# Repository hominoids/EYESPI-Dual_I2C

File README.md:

# EYESPI-Dual_I2C

## Introduction
EYESPI-Dual_I2C is an EYESPI display port and dual I2C 5 port hubs that can be deployed with passive or active termination on most SBC using their 40 pin GPIO. 

License: GPLv3.

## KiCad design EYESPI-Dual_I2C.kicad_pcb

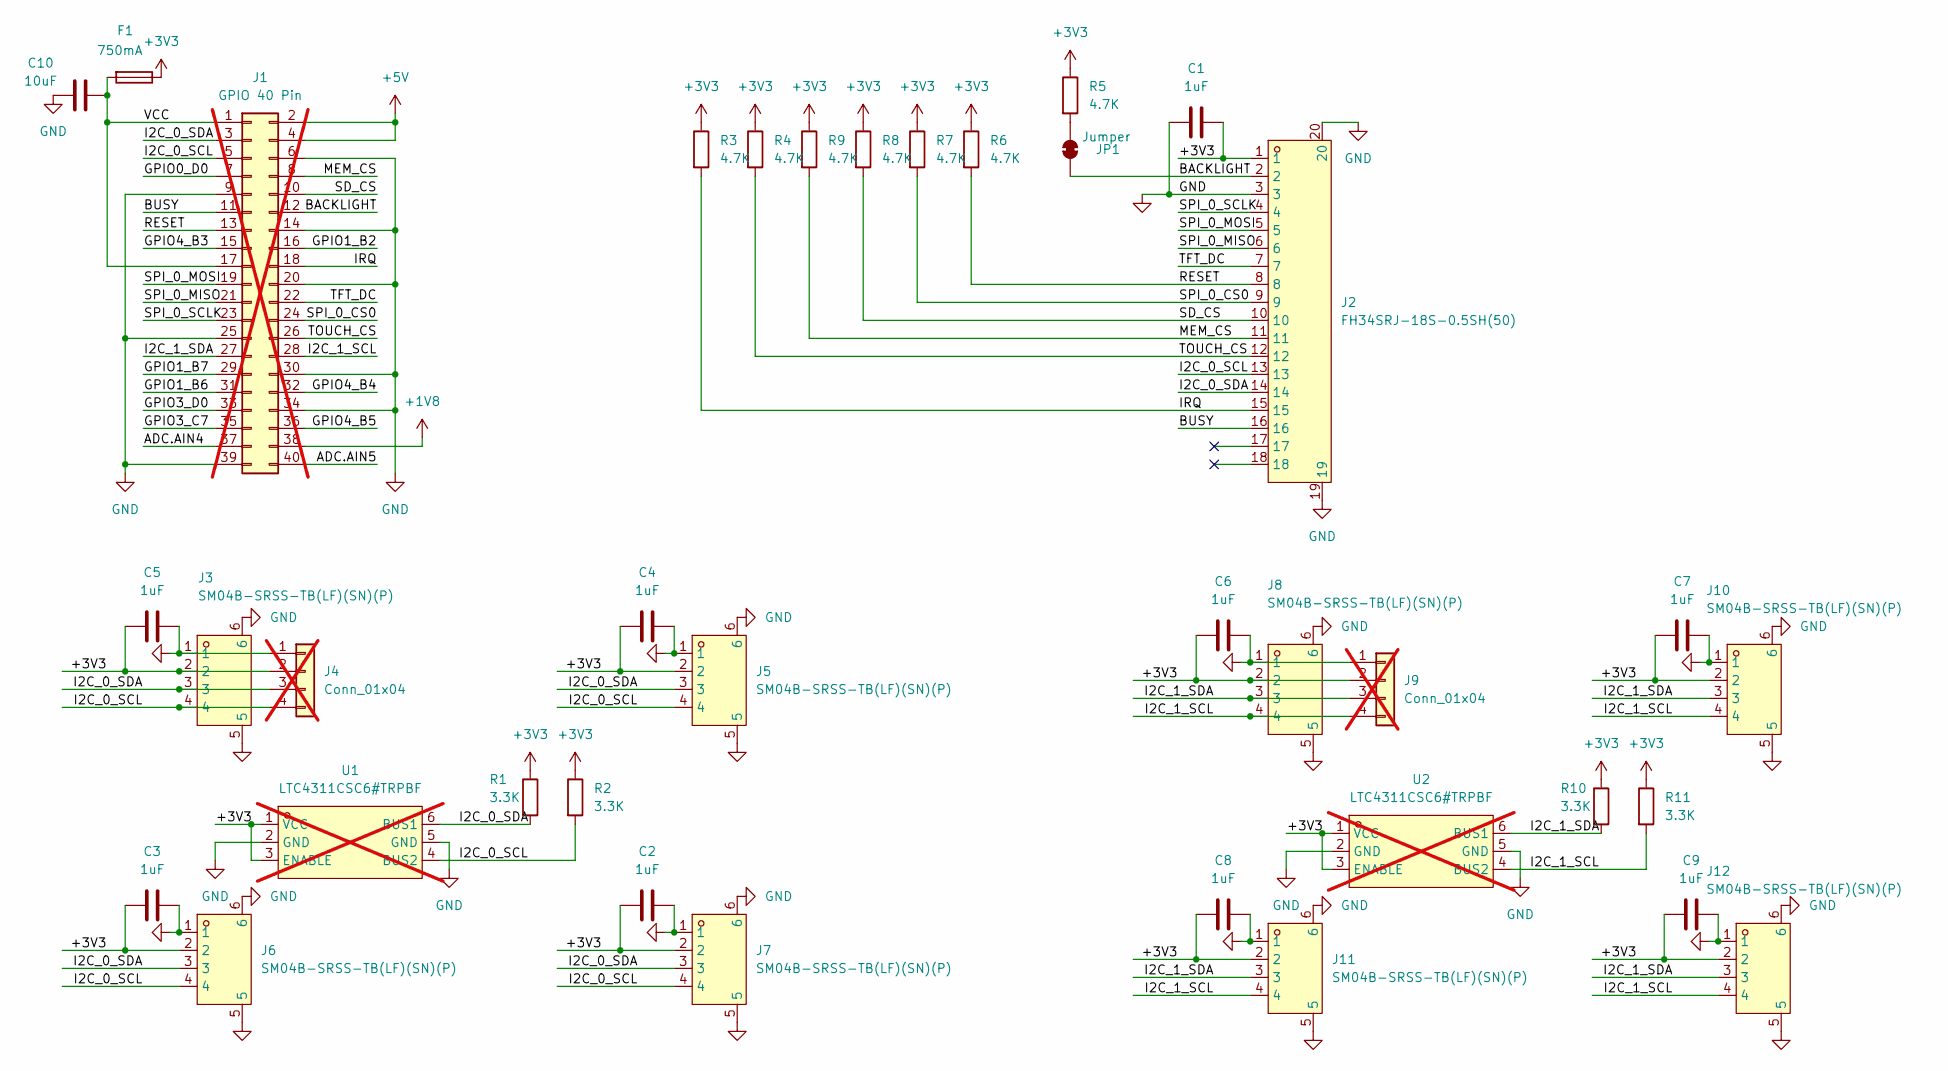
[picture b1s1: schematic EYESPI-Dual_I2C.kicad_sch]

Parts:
C1, C2, C3, C4, C5, C6, C7, C8, C9: 1uF; C_0603_1608Metric
C10: 10uF; C_0603_1608Metric
F1: 750mA; Fuse_1206_3216Metric
J1: GPIO 40 Pin; PinSocket_2x20_P2.54mm_Vertical; not fitted
J2: FH34SRJ-18S-0.5SH(50); FFC-SMD_18P-P0.50_FH34SRJ-18S-0.5SH; LCSC Part C3169386
J3, J5, J6, J7, J8, J10, J11, J12: SM04B-SRSS-TB(LF)(SN)(P); CONN-SMD_4P-P1.00_SM04B-SRSS-TB-LF-SN; LCSC Part C28867426
J4, J9: Conn_01x04; PinHeader_1x04_P2.54mm_Horizontal; not fitted
JP1: Jumper; SolderJumper-2_P1.3mm_Bridged2Bar_RoundedPad1.0x1.5mm
R1, R2, R10, R11: 3.3K; R_0603_1608Metric
R3, R4, R5, R6, R7, R8, R9: 4.7K; R_0603_1608Metric
U1, U2: LTC4311CSC6#TRPBF; SC-70-6_L2.1-W1.3-P0.65-LS2.1-BR; LCSC Part C580856; not fitted

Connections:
+1V8: J1.38
+3V3: C1.1, C2.1, C3.1, C4.1, C5.1, C6.1, C7.1, C8.1, C9.1, F1.1, J2.1, J3.2, J4.2, J5.2, J6.2, J7.2, J8.2, J9.2, J10.2, J11.2, J12.2, R1.1, R2.1, R3.1, R4.1, R5.1, R6.1, R7.1, R8.1, R9.1, R10.1, R11.1, U1.1 (VCC), U1.3 (ENABLE), U2.1 (VCC), U2.3 (ENABLE)
+5V: J1.2, J1.4
/ADC.AIN4: J1.37
/ADC.AIN5: J1.40
/BACKLIGHT: J1.12, J2.2, JP1.2 (B)
/BUSY: J1.11, J2.16
/GPIO0_D0: J1.7
/GPIO1_B2: J1.16
/GPIO1_B6: J1.31
/GPIO1_B7: J1.29
/GPIO3_C7: J1.35
/GPIO3_D0: J1.33
/GPIO4_B3: J1.15
/GPIO4_B4: J1.32
/GPIO4_B5: J1.36
/I2C_0_SCL: J1.5, J2.13, J3.4, J4.4, J5.4, J6.4, J7.4, R2.2, U1.4 (BUS2)
/I2C_0_SDA: J1.3, J2.14, J3.3, J4.3, J5.3, J6.3, J7.3, R1.2, U1.6 (BUS1)
/I2C_1_SCL: J1.28, J8.4, J9.4, J10.4, J11.4, J12.4, R11.2, U2.4 (BUS2)
/I2C_1_SDA: J1.27, J8.3, J9.3, J10.3, J11.3, J12.3, R10.2, U2.6 (BUS1)
/IRQ: J1.18, J2.15, R3.2
/MEM_CS: J1.8, J2.11, R9.2
/RESET: J1.13, J2.8, R6.2
/SD_CS: J1.10, J2.10, R8.2
/SPI_0_CS0: J1.24, J2.9, R7.2
/SPI_0_MISO: J1.21, J2.6
/SPI_0_MOSI: J1.19, J2.5
/SPI_0_SCLK: J1.23, J2.4
/TFT_DC: J1.22, J2.7
/TOUCH_CS: J1.26, J2.12, R4.2
/VCC: C10.2, F1.2, J1.1, J1.17
GND: C1.2, C2.2, C3.2, C4.2, C5.2, C6.2, C7.2, C8.2, C9.2, C10.1, J1.6, J1.9, J1.14, J1.20, J1.25, J1.30, J1.34, J1.39, J2.3, J2.19, J2.20, J3.1, J3.5, J3.6, J4.1, J5.1, J5.5, J5.6, J6.1, J6.5, J6.6, J7.1, J7.5, J7.6, J8.1, J8.5, J8.6, J9.1, J10.1, J10.5, J10.6, J11.1, J11.5, J11.6, J12.1, J12.5, J12.6, U1.2 (GND), U1.5 (GND), U2.2 (GND), U2.5 (GND)
unnamed: JP1.1 (A), R5.2

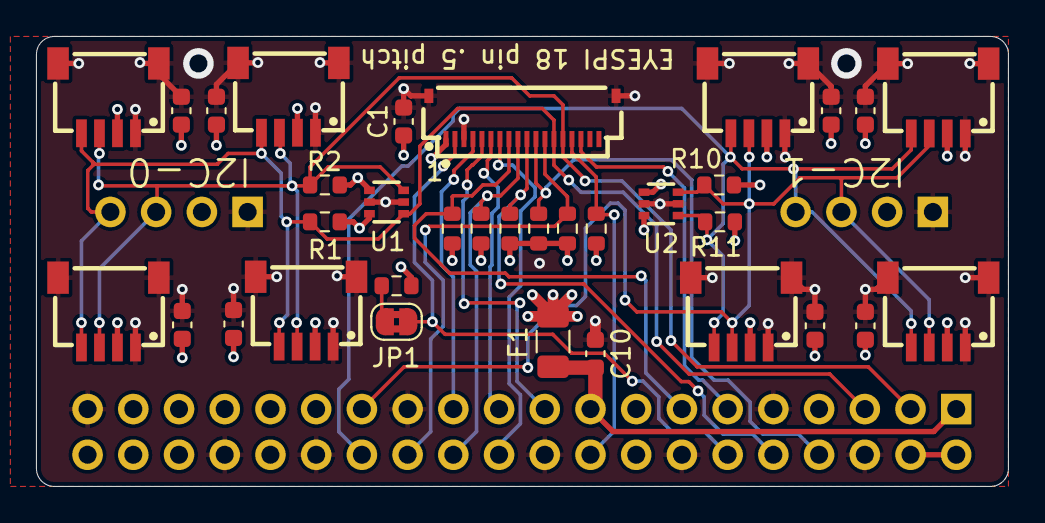
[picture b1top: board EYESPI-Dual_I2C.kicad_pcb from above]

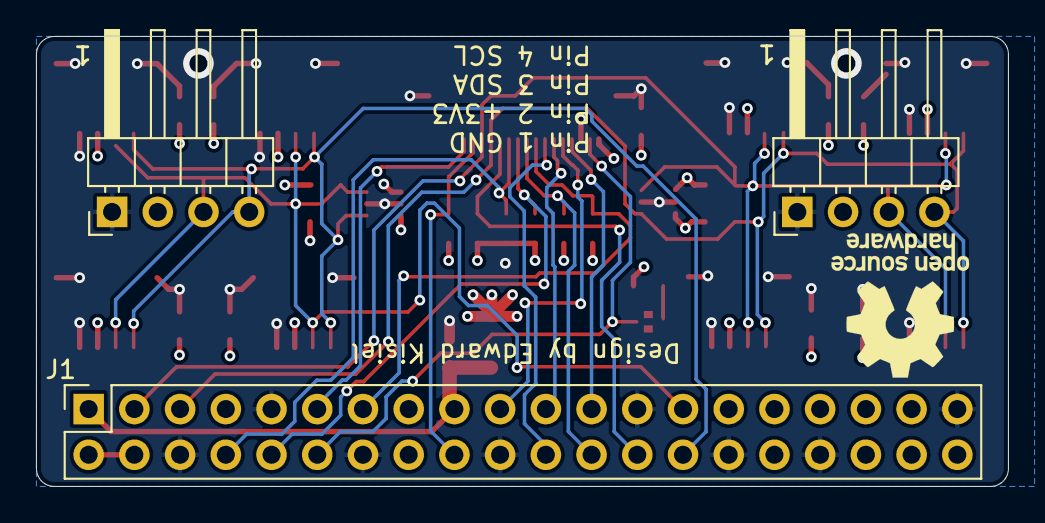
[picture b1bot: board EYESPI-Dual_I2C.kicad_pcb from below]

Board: 4 copper layers, 54.0 x 25.0 mm, 37 parts (3 on the bottom side), 21 nets.

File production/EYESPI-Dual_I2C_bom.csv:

Designator,Footprint,Quantity,Value,LCSC Part #
"C1, C2, C3, C4, C5, C6, C7, C8, C9",0603,9,1uF,
C10,0603,1,10uF,
F1,1206,1,750mA,
J1,PinSocket_2x20_P2.54mm_Vertical,1,GPIO 40 Pin,
"J10, J11, J12, J3, J5, J6, J7, J8",CONN-SMD_4P-P1.00_SM04B-SRSS-TB-LF-SN,8,SM04B-SRSS-TB(LF)(SN)(P),
J2,FFC-SMD_18P-P0.50_FH34SRJ-18S-0.5SH,1,FH34SRJ-18S-0.5SH(50),
"J4, J9",PinHeader_1x04_P2.54mm_Horizontal,2,Conn_01x04,
"R1, R10, R11, R2",0603,4,3.3K,
"R3, R4, R5, R6, R7, R8, R9",0603,7,4.7K,
"U1, U2",SC-70-6_L2.1-W1.3-P0.65-LS2.1-BR,2,LTC4311CSC6#TRPBF,
